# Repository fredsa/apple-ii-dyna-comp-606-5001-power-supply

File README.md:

# Apple II 605-5703 (DynaComp 606-5001) Power Supply 110v

- KiCad schematic reverse-engineered by Fred Sauer in 2025, 2026.

- Part numbers and compontent layout updated to match power supply schematic
  published in _The Apple II Circuit Description_ (reprint of
  _Apple II Reference Manual 1981_), except for differences indicated by dotted
  outlines marked `diff`.

- Refer to [U.S. Patent 4,130,862](https://patents.google.com/patent/US4130862A)
  for an explanation of key design features of this power supply.

- KiCad and PDF schematic can be found in the `Dyna-Comp-606-5001-KiCad/`
  folder.

<hr>

<table>
  <caption>KiCad schematic</caption>
  <tr>
    <td>
      <a href="Dyna-Comp-606-5001-KiCad.svg">Dyna-Comp-606-5001-KiCad.svg</a><br>
      <a href="Dyna-Comp-606-5001-KiCad.pdf">Dyna-Comp-606-5001-KiCad.pdf</a><br>
    </td>
  </tr>
  <tr>
    <td></td>
  </tr>
</table>

<table>
  <caption>Main circuit board</caption>
  <tr>
    <td>Bottom side (flipped)</td>
    <td>Top side</td>
  </tr>
  <tr>
    <td></td>
    <td></td>
  </tr>
</table>

<table>
  <caption>Line filter</caption>
  <tr>
    <td></td>
  </tr>
</table>

Model number `606-5001`

Specifications: `120 VAC` `60 Hz, 1 AMP`

Made in `DynaComp, Richardson, TX`:

<table>
  <caption>Line filter</caption>
  <tr>
    <td></td>
    <td></td>
  </tr>
</table>

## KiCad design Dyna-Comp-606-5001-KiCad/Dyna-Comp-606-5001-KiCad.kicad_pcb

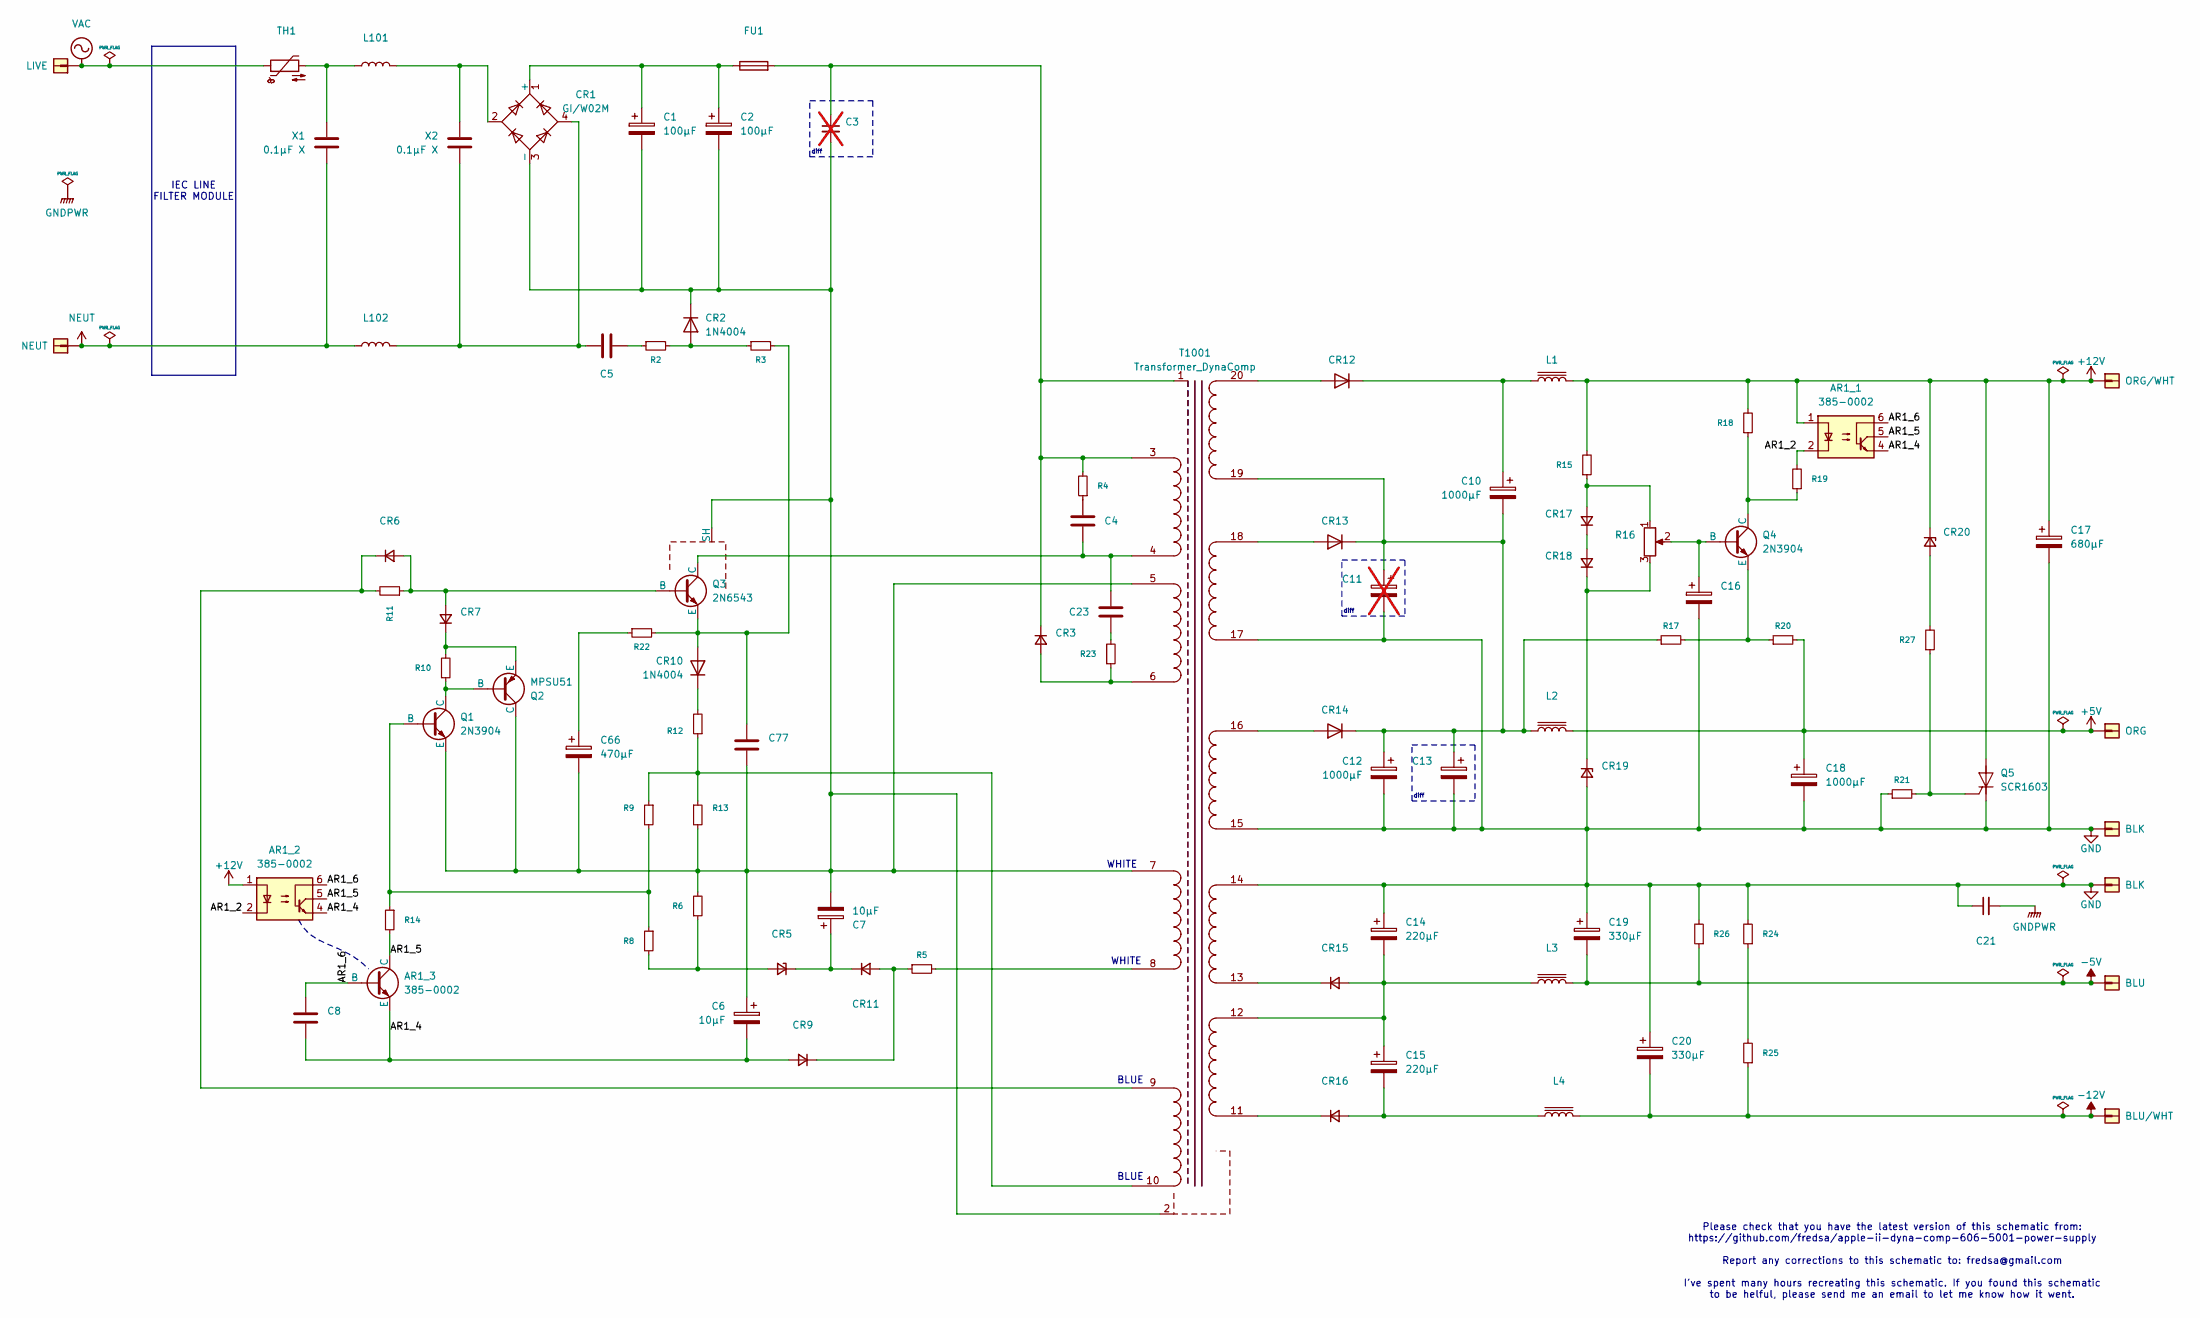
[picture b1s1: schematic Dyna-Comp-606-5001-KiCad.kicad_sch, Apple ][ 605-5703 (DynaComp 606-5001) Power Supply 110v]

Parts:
AR1_1, AR1_2: 385-0002; DIP-6_W7.62mm
AR1_3: 385-0002
C1, C2: 100µF; CP_Radial_D10.0mm_P7.50mm
C3: C; not fitted
C4: C; C_Disc_D4.3mm_W1.9mm_P5.00mm
C5: C; C_Axial_L17.0mm_D6.5mm_P25.00mm_Horizontal
C6, C7: 10µF; -CP_Axial_P20.5mm_Horizontal
C8: C; C_Disc_D10.0mm_W2.5mm_P5.00mm
C10, C12, C18: 1000µF; CP_Radial_Tantal_D4.5mm_P5.00mm
C11: C; CP_Radial_Tantal_D4.5mm_P5.00mm; not fitted
C13: C; CP_Radial_Tantal_D4.5mm_P5.00mm
C14, C15: 220µF; CP_Radial_Tantal_D4.5mm_P5.00mm
C16: C; CP_Axial_L11.0mm_D5.0mm_P18.00mm_Horizontal
C17: 680µF; CP_Radial_Tantal_D4.5mm_P5.00mm
C19, C20: 330µF; CP_Radial_Tantal_D4.5mm_P5.00mm
C21: C_Small; C_Disc_D10.5mm_W5.0mm_P10.00mm
C23, C77: C; C_Rect_L11.0mm_W2.8mm_P10.00mm_MKT
C66: 470µF; CP_Radial_Tantal_D4.5mm_P5.00mm
CR1: GI/W02M; Diode_Bridge_Round_D9.0mm
CR2, CR10: 1N4004; D_DO-34_SOD68_P12.70mm_Horizontal
CR3, CR6, CR7, CR9, CR11, CR15, CR16, CR17, CR18: D_Small; D_DO-34_SOD68_P12.70mm_Horizontal
CR5, CR20: D_Zener_Small; D_A-405_P12.70mm_Horizontal
CR12, CR13, CR14: D; -D_P10mm_Vertical_CathodeUp-Heatsink
CR19: D_Zener_Small; D_DO-34_SOD68_P10.16mm_Horizontal
FU1: Fuse; Fuse_SunFuse-6HP
J1001, J1002, J1003, J1004, J1005, J1006, J1007, J1008: Conn_01x01; SolderWire-0.25sqmm_1x01_D0.65mm_OD1.7mm
L1, L2, L3, L4: -L_Axial_P9mm
L101, L102: L; -L_Toroid_Vertical_P8.40mm
Q1, Q4: 2N3904; -TO-92_Wide-pin2-fwd
Q2: MPSU51; TO-220F-3_Vertical
Q3: 2N6543; TO-3
Q5: SCR1603; TO-220F-3_Vertical
R2, R3, R4, R5, R6, R8, R9, R10, R11, R12, R13, R14, R15, R17, R18, R20, R21, R22, R23, R24, R25, R26, R27: R_Small; -R_Axial_P12.70mm_Horizontal
R16: R_Potentiometer; Potentiometer_Runtron_RM-063_Horizontal
R19: R_Small; R_Axial_DIN0207_L6.3mm_D2.5mm_P10.16mm_Horizontal
T1001: Transformer_DynaComp; Transformer_EPCOS_B66359J1014T_Vertical
TH1: Thermistor_NTC; R_Axial_DIN0204_L3.6mm_D1.6mm_P5.08mm_Horizontal
X1, X2: 0.1µF X; C_Rect_L16.5mm_W4.9mm_P15.00mm_MKT

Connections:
+5V: C18.1, J1002.1 (ORG_1), L2.2, R20.2
+12V: AR1_1.1, AR1_2.1, C17.1, CR20.1 (K), J1001.1 (ORG/WHT_1), L1.2, Q5.2 (A), R15.2, R18.2
-5V: C19.2, J1005.1 (BLU_1), L3.2, R26.1
-12V: C20.2, J1006.1 (BLU/WHT_1), L4.2, R25.1
/AR1_2: AR1_1.2, AR1_2.2, R19.2
/AR1_4: AR1_1.4, AR1_2.4, AR1_3.1 (E), C6.2, C8.1, CR9.2 (A)
/AR1_5: AR1_1.5, AR1_2.5, AR1_3.3 (C), R14.2
/AR1_6: AR1_1.6, AR1_2.6, AR1_3.2 (B), C8.2
GND: C11.2, C12.2, C13.2, C14.1, C16.2, C17.2, C18.2, C19.1, C20.1, C21.1, CR19.2 (A), J1003.1 (BLK_1), J1004.1 (BLK_1), Q5.3 (K), R21.1, R24.2, R26.2, T1001.14 (SD), T1001.15 (SE), T1001.17 (SG)
GNDPWR: C21.2
NEUT: J1007.1 (NEUT_1), L102.1, X1.2
unnamed: C4.1, R4.1
unnamed: C5.1, R2.1
unnamed: C5.2, CR1.4, L102.2, X2.2
unnamed: C23.2, R23.2
unnamed: C66.1, R22.1
unnamed: C1.1, C2.1, CR1.1 (+), FU1.1
unnamed: C1.2, C2.2, C3.2, C6.1, C7.2, C66.2, C77.1, CR1.3 (-), CR2.1 (K), Q1.1 (E), Q2.1 (C), Q3.0 (SH), R6.2, R13.2, T1001.2 (SH), T1001.5 (AC), T1001.7 (AE)
unnamed: CR1.2, L101.2, X2.1
unnamed: CR2.2 (A), R2.2, R3.1
unnamed: CR3.2 (A), R23.1, T1001.6 (AD)
unnamed: C3.1, CR3.1 (K), FU1.2, R4.2, T1001.1 (CORE), T1001.3 (AA)
unnamed: CR5.2 (A), R6.1, R8.2
unnamed: CR6.2 (A), CR7.2 (A), Q3.1 (B), R11.1
unnamed: CR6.1 (K), R11.2, T1001.9 (AG)
unnamed: CR7.1 (K), Q2.3 (E), R10.2
unnamed: C77.2, CR10.2 (A), Q3.2 (E), R3.2, R22.2
unnamed: CR10.1 (K), R12.2
unnamed: CR9.1 (K), CR11.2 (A), R5.1
unnamed: C7.1, CR5.1 (K), CR11.1 (K)
unnamed: CR12.2 (A), T1001.20 (SJ)
unnamed: C10.1, CR12.1 (K), L1.1
unnamed: CR13.2 (A), T1001.18 (SH)
unnamed: C10.2, C11.1, C12.1, C13.1, CR13.1 (K), CR14.1 (K), L2.1, R17.1, T1001.19 (SI)
unnamed: CR14.2 (A), T1001.16 (SF)
unnamed: C14.2, C15.1, CR15.2 (A), L3.1, T1001.12 (SB)
unnamed: CR15.1 (K), T1001.13 (SC)
unnamed: C15.2, CR16.2 (A), L4.1
unnamed: CR16.1 (K), T1001.11 (SA)
unnamed: CR17.2 (A), R15.1, R16.1
unnamed: CR17.1 (K), CR18.2 (A)
unnamed: CR18.1 (K), CR19.1 (K), R16.3
unnamed: CR20.2 (A), R27.2
unnamed: L101.1, TH1.2, X1.1
unnamed: Q1.2 (B), R8.1, R9.2, R14.1
unnamed: Q1.3 (C), Q2.2 (B), R10.1
unnamed: C4.2, C23.1, Q3.3 (C), T1001.4 (AB)
unnamed: C16.1, Q4.2 (B), R16.2
unnamed: Q4.3 (C), R18.1, R19.1
unnamed: Q4.1 (E), R17.2, R20.1
unnamed: Q5.1 (G), R21.2, R27.1
unnamed: R24.1, R25.2
unnamed: R5.2, T1001.8 (AF)
unnamed: R9.1, R12.1, R13.1, T1001.10 (AH)
VAC: J1008.1 (LIVE_1), TH1.1

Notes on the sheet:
WHITE
IEC LINE FILTER MODULE
BLUE
diff
Please check that you have the latest version of this schematic from: https://github.com/fredsa/apple-ii-dyna-comp-606-5001-power-supply Report any corrections to this schematic to: fredsa@gmail.com I've spent many hours recreating this schematic. If you found this schematic to be helful, please se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

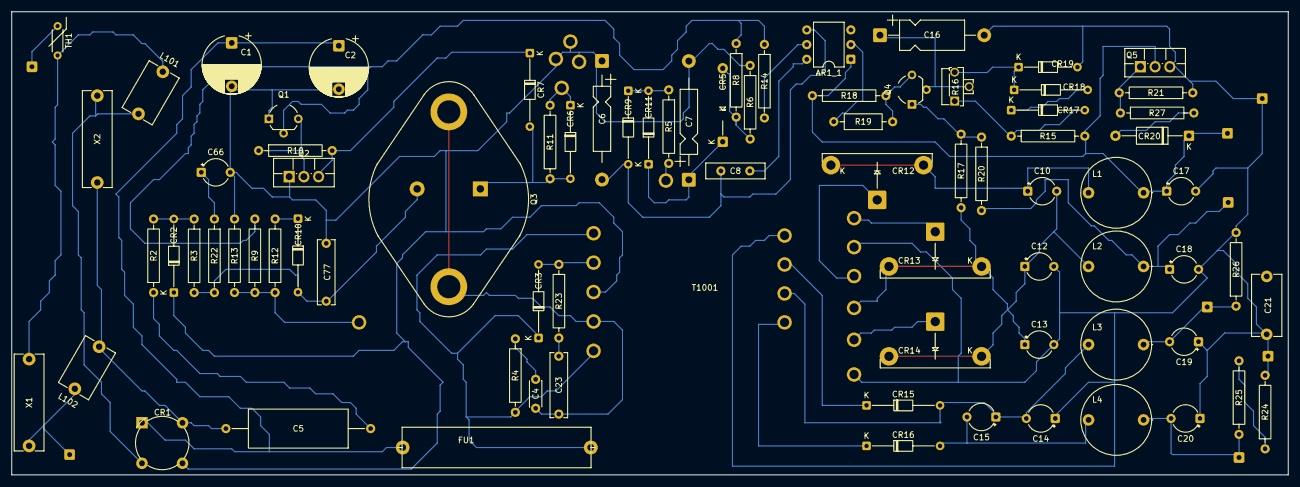
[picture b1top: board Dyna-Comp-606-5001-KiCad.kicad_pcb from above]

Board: 2 copper layers, 220.5 x 80.0 mm, 89 parts (0 on the bottom side), 54 nets.

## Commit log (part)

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2025-11-04 Photos
2025-11-04 Apache 2.0 License
2025-11-04 README
2025-11-04 GIMP composite image
2025-11-04 Reverse-engineered KiCad files
2025-11-04 gitignore
2025-11-04 Updated schematic title to include Apple part number
2025-11-21 Updated photos and README
